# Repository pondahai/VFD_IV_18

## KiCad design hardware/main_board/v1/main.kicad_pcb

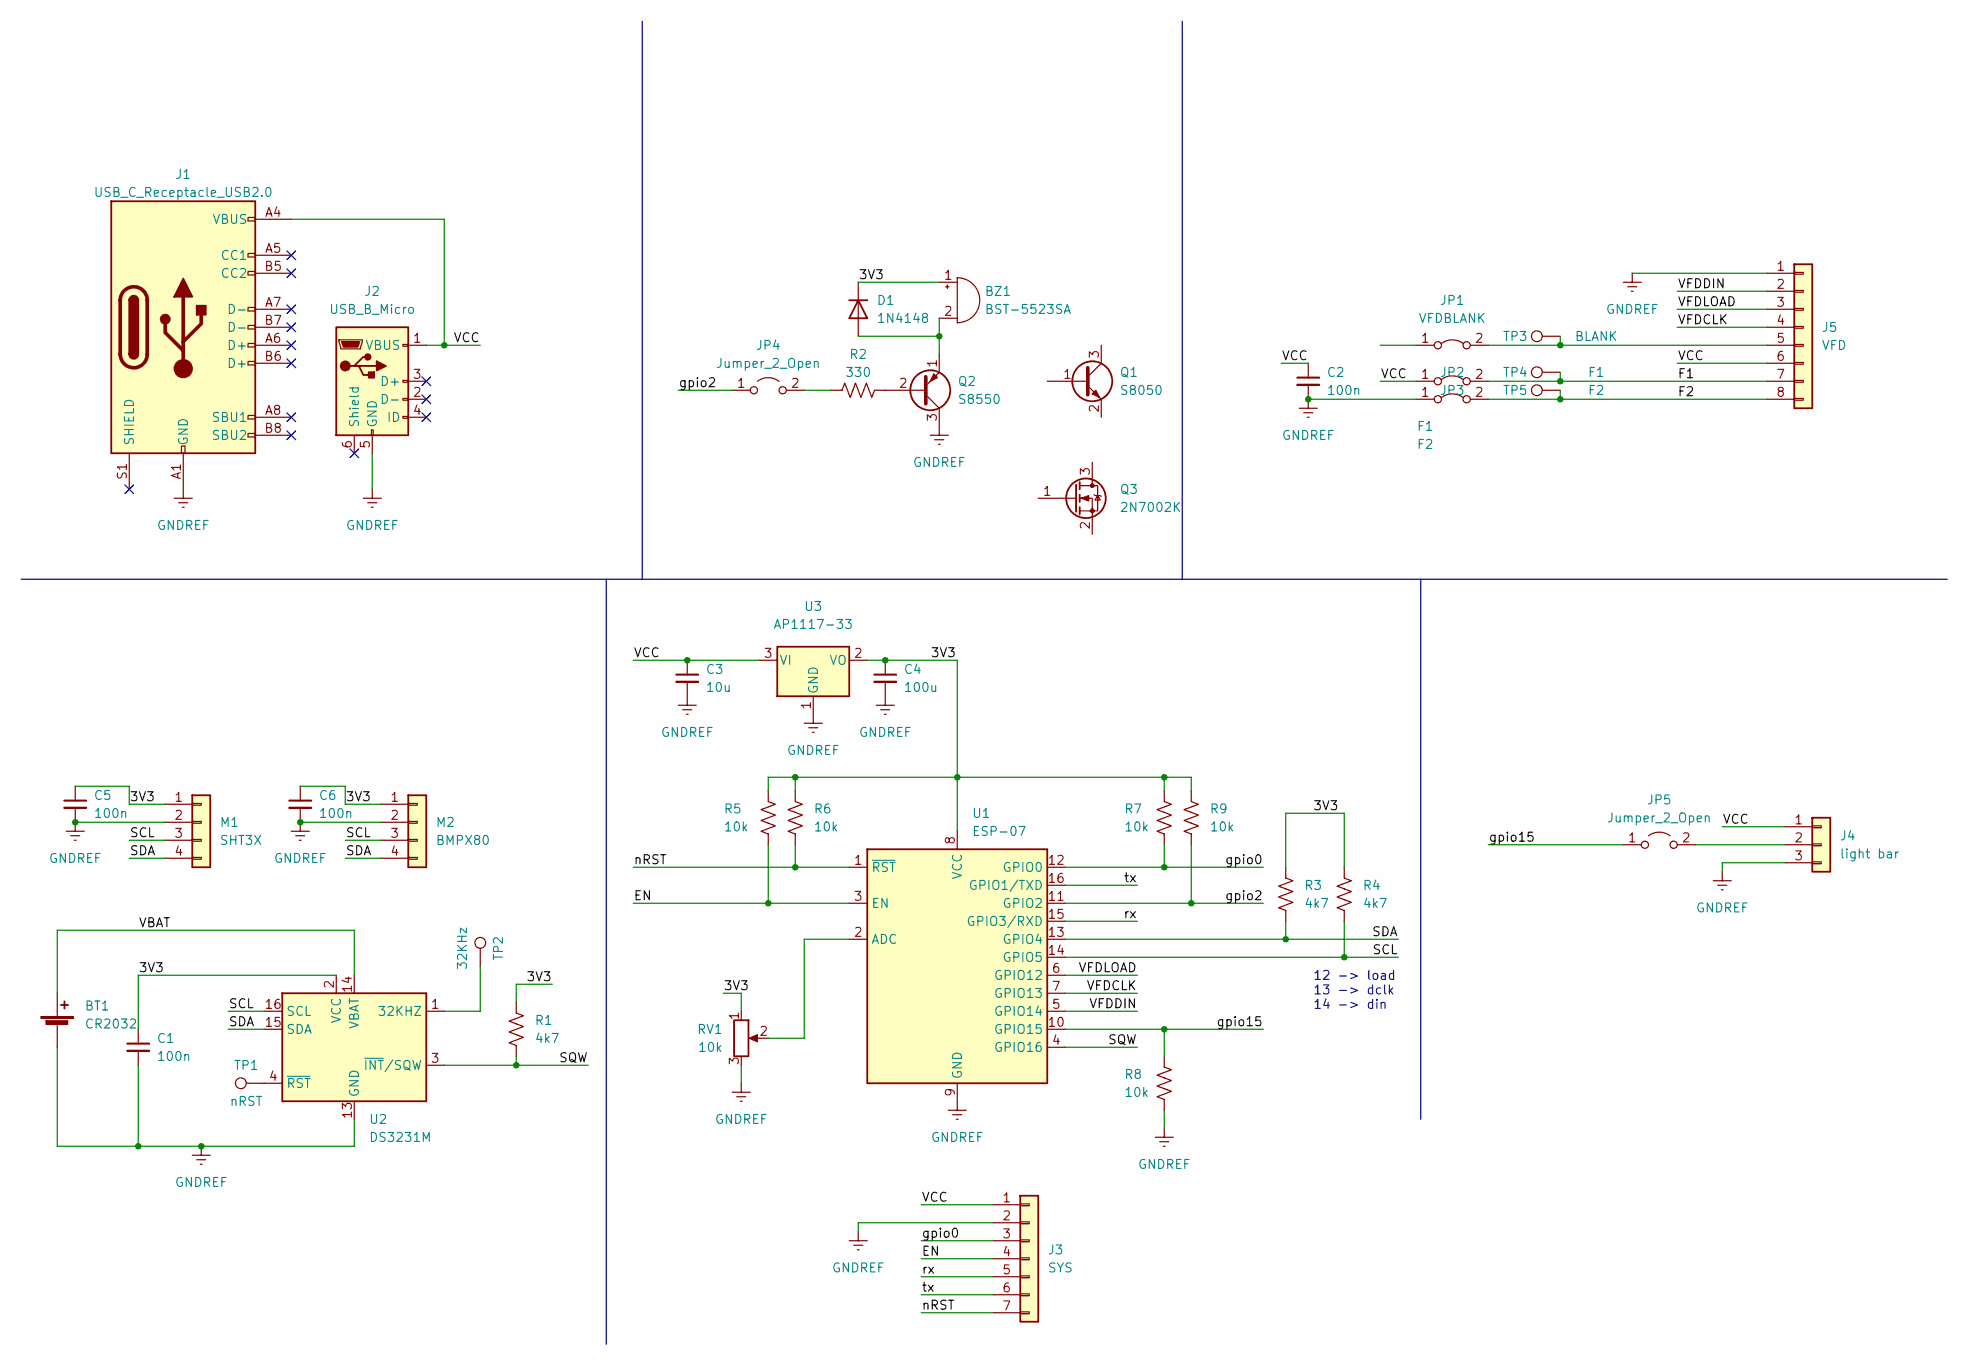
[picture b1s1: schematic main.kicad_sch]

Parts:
BT1: CR2032; BatteryHolder_Keystone_3002_1x2032
BZ1: BST-5523SA
C1, C2, C5, C6: 100n; C_0805_2012Metric_Pad1.18x1.45mm_HandSolder
C3: 10u; C_1206_3216Metric_Pad1.33x1.80mm_HandSolder
C4: 100u; C_1206_3216Metric_Pad1.33x1.80mm_HandSolder
D1: 1N4148; D_1206_3216Metric_Pad1.42x1.75mm_HandSolder
J1: USB_C_Receptacle_USB2.0; USB_C_Receptacle_Palconn_UTC16-G
J2: USB_B_Micro; USB_Micro-B_GCT_USB3076-30-A
J3: SYS; PinHeader_1x07_P2.54mm_Vertical
J4: light bar; PinHeader_1x03_P2.54mm_Vertical
J5: VFD; PinHeader_1x08_P2.54mm_Vertical
JP1: VFDBLANK; SolderJumper-2_P1.3mm_Bridged_RoundedPad1.0x1.5mm
JP2: F1; SolderJumper-2_P1.3mm_Bridged_RoundedPad1.0x1.5mm
JP3: F2; SolderJumper-2_P1.3mm_Bridged_RoundedPad1.0x1.5mm
JP4, JP5: Jumper_2_Open; SolderJumper-2_P1.3mm_Bridged_RoundedPad1.0x1.5mm
M1: SHT3X; PinHeader_1x04_P2.54mm_Vertical
M2: BMPX80; PinHeader_1x04_P2.54mm_Vertical
Q1: S8050; SOT-23
Q2: S8550; TO-92_Inline
Q3: 2N7002K; SOT-23
R1, R3, R4: 4k7; R_0805_2012Metric_Pad1.20x1.40mm_HandSolder
R2: 330; R_0805_2012Metric_Pad1.20x1.40mm_HandSolder
R5, R6, R7, R8, R9: 10k; R_0805_2012Metric_Pad1.20x1.40mm_HandSolder
RV1: 10k; Potentiometer_Bourns_PTA2043_Single_Slide
TP1: nRST; TestPoint_Pad_D1.0mm
TP2: 32KHz; TestPoint_Pad_D1.0mm
TP3: BLANK; TestPoint_Pad_D1.0mm
TP4: F1; TestPoint_Pad_D1.0mm
TP5: F2; TestPoint_Pad_D1.0mm
U1: ESP-07
U2: DS3231M; SOIC-16W_7.5x10.3mm_P1.27mm
U3: AP1117-33; SOT-223-3_TabPin2

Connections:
/3V3: BZ1.1 (-), C1.1, C4.1, C5.1, C6.1, D1.1 (K), M1.1, M2.1, R1.1, R3.1, R4.1, R5.1, R6.1, R7.1, R9.1, RV1.1, U1.8 (VCC), U2.2 (VCC), U3.2 (VO)
/EN: J3.4, R5.2, U1.3 (EN)
/F1: J5.7, JP2.2 (B), TP4.1
/F2: J5.8, JP3.2 (B), TP5.1
/SCL: M1.3, M2.3, R4.2, U1.14 (GPIO5), U2.16 (SCL)
/SDA: M1.4, M2.4, R3.2, U1.13 (GPIO4), U2.15 (SDA)
/SQW: R1.2, U1.4 (GPIO16), U2.3 (~INT/SQW)
/VBAT: BT1.1 (+), U2.14 (VBAT)
/VCC: C2.1, C3.1, J1.A4 (VBUS), J1.A9 (VBUS), J1.B4 (VBUS), J1.B9 (VBUS), J2.1 (VBUS), J3.1, J4.1, J5.6, JP2.1 (A), U3.3 (VI)
/VFDCLK: J5.4, U1.7 (GPIO13)
/VFDDIN: J5.2, U1.5 (GPIO14)
/VFDLOAD: J5.3, U1.6 (GPIO12)
/gpio0: J3.3, R7.2, U1.12 (GPIO0)
/gpio2: JP4.1 (A), R9.2, U1.11 (GPIO2)
/gpio15: JP5.1 (A), R8.1, U1.10 (GPIO15)
/nRST: J3.7, R6.2, U1.1 (~RST)
/rx: J3.5, U1.15 (GPIO3/RXD)
/tx: J3.6, U1.16 (GPIO1/TXD)
GNDREF: BT1.2 (-), C1.2, C2.2, C3.2, C4.2, C5.2, C6.2, J1.A1 (GND), J1.A12 (GND), J1.B1 (GND), J1.B12 (GND), J2.5 (GND), J3.2, J4.3, J5.1, JP3.1 (A), M1.2, M2.2, Q2.3 (C), R8.2, RV1.3, U1.9 (GND), U2.5 (GND), U2.6 (GND), U2.7 (GND), U2.8 (GND), U2.9 (GND), U2.10 (GND), U2.11 (GND), U2.12 (GND), U2.13 (GND), U3.1 (GND)
unnamed: BZ1.2 (+), BZ1.3, D1.2 (A), Q2.1 (E)
unnamed: J4.2, JP5.2 (B)
unnamed: J5.5, JP1.2 (B), TP3.1
unnamed: JP4.2 (B), R2.1
unnamed: Q2.2 (B), R2.2
unnamed: RV1.2, U1.2 (ADC)
unnamed: TP1.1, U2.4 (~RST)
unnamed: TP2.1, U2.1 (32KHZ)

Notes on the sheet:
12 -> load 13 -> dclk 14 -> din

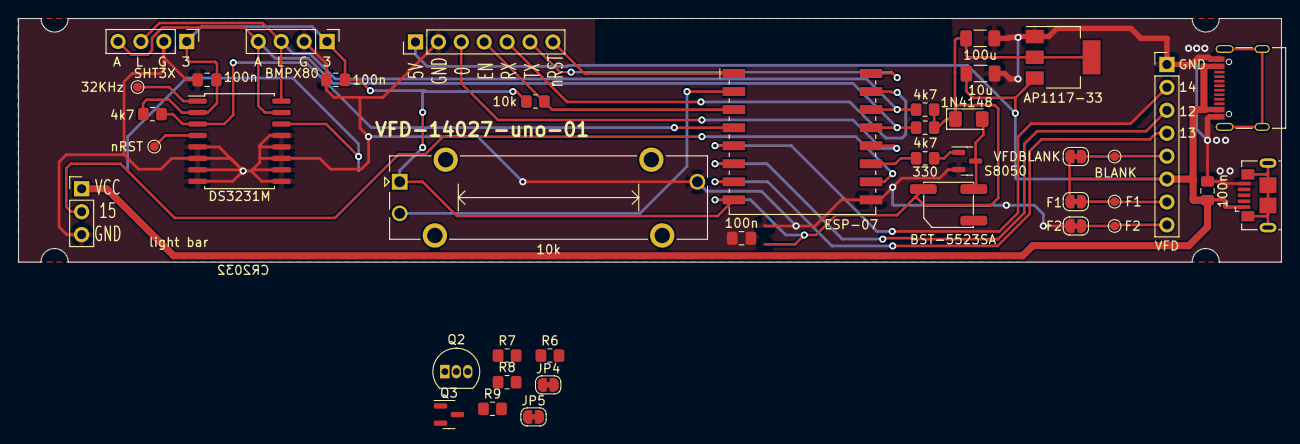
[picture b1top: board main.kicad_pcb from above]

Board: 2 copper layers, 140.0 x 27.0 mm, 42 parts (1 on the bottom side), 27 nets.

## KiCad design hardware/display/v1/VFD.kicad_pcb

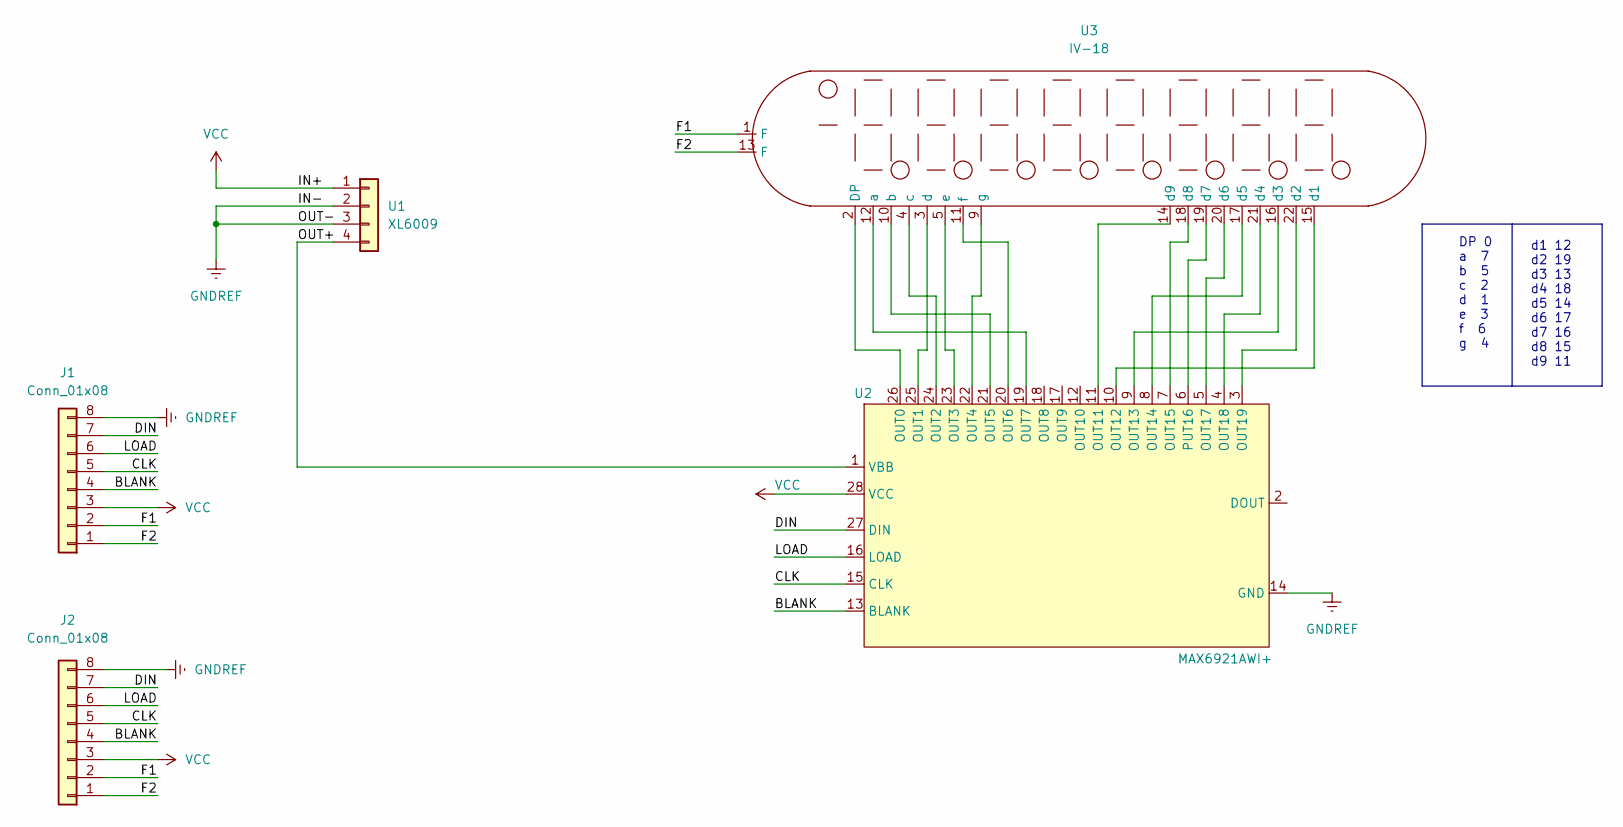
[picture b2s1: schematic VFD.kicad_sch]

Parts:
J1, J2: Conn_01x08; PinHeader_1x08_P2.54mm_Horizontal
U1: XL6009
U2: MAX6921AWI+; SOIC-28W_7.5x18.7mm_P1.27mm
U3: IV-18; IV-18_BOTTOM_VIEW

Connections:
/BLANK: J1.4, J2.4, U2.13 (BLANK)
/CLK: J1.5, J2.5, U2.15 (CLK)
/DIN: J1.7, J2.7, U2.27 (DIN)
/F1: J1.2, J2.2, U3.1 (F)
/F2: J1.1, J2.1, U3.13 (F)
/LOAD: J1.6, J2.6, U2.16 (LOAD)
/OUT+: U1.4, U2.1 (VBB)
GNDREF: J1.8, J2.8, U1.2, U1.3, U2.14 (GND)
unnamed: U2.3 (OUT19), U3.22 (d2)
unnamed: U2.4 (OUT18), U3.21 (d4)
unnamed: U2.5 (OUT17), U3.20 (d6)
unnamed: U2.6 (PUT16), U3.19 (d7)
unnamed: U2.7 (OUT15), U3.18 (d8)
unnamed: U2.8 (OUT14), U3.17 (d5)
unnamed: U2.9 (OUT13), U3.16 (d3)
unnamed: U2.10 (OUT12), U3.15 (d1)
unnamed: U2.11 (OUT11), U3.14 (d9)
unnamed: U2.19 (OUT7), U3.12 (a)
unnamed: U2.20 (OUT6), U3.11 (f)
unnamed: U2.21 (OUT5), U3.10 (b)
unnamed: U2.22 (OUT4), U3.9 (g)
unnamed: U2.23 (OUT3), U3.5 (e)
unnamed: U2.24 (OUT2), U3.4 (c)
unnamed: U2.25 (OUT1), U3.3 (d)
unnamed: U2.26 (OUT0), U3.2 (DP)
VCC: J1.3, J2.3, U1.1, U2.28 (VCC)

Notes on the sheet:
d1 12 d2 19 d3 13 d4 18 d5 14 d6 17 d7 16 d8 15 d9 11
DP 0 a 7 b 5 c 2 d 1 e 3 f 6 g 4

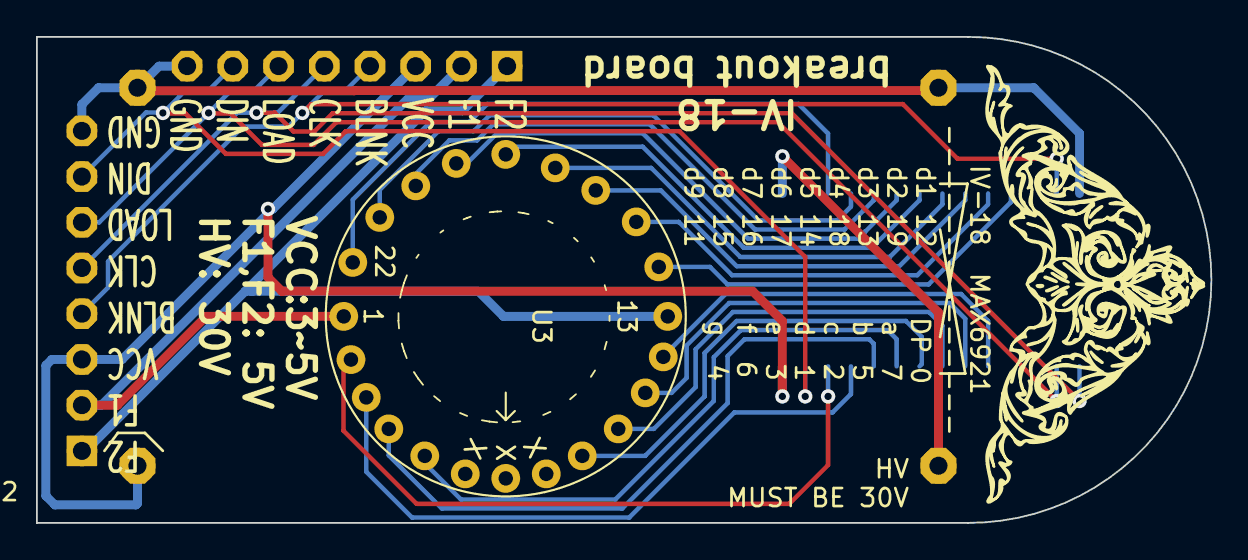
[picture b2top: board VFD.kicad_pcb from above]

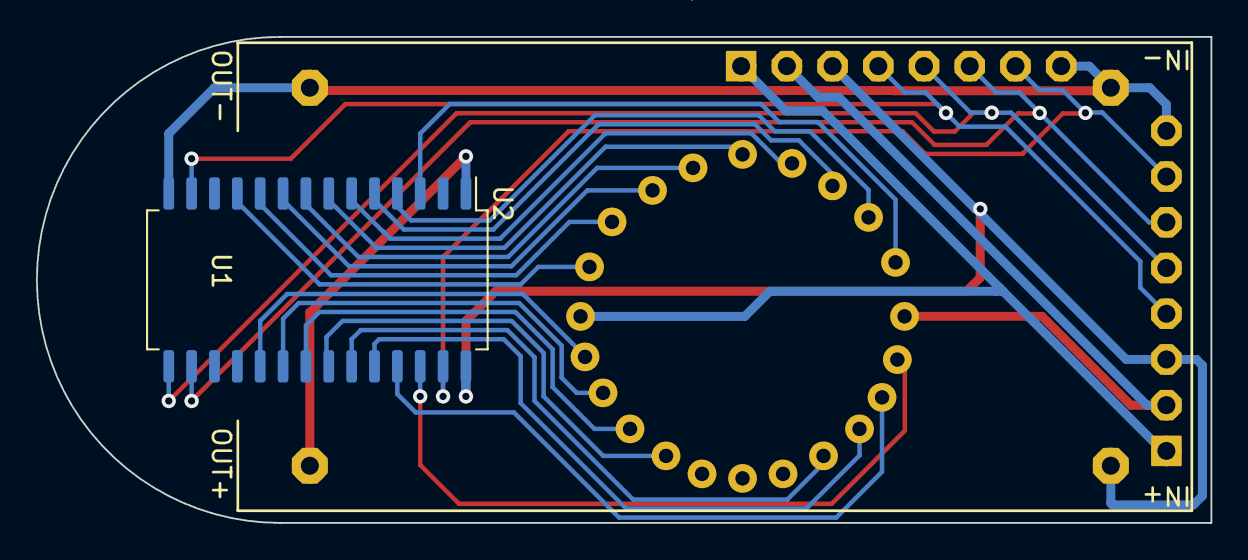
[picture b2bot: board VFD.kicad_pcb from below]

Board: 2 copper layers, 65.2 x 27.0 mm, 5 parts (3 on the bottom side), 26 nets.

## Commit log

2023-02-26 add calculator
